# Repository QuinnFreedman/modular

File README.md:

This project is an attempt to make Eurorack modular synthesis affordable and accessible to everyone.

This repository contains open source software and hardware schematics for Eurorack modules which are designed to be assembled easily and cheaply without any technical knowledge. Every module should be able to be assembled for around $20 in about an hour of work, even with limited experience.

To get started, check out some of the links below. Or get in touch! Send me a message at <a href="mailto:freemodular@gmail.com">freemodular@gmail.com</a>. Follow my <a href="https://www.reddit.com/user/FreeModular/submitted/">reddit</a>, <a href="https://freemodular.etsy.com/">Etsy shop</a>, or <a href="https://github.com/QuinnFreedman/modular">GitHub</a>.

**Happy travels on your modular journey!**

<a style="display:none" href="https://freemodular.org">Go to the website to see more</a>

<h2 style="display:none">Links</h2>
<ul class="fm-index-links-container">
  <li>
    <a href="https://freemodular.org/docs/about-eurorack" class="fm-hidden-link fm-index-link">
      About Eurorack
    </a>
  </li>
  <li>
    <a href="https://freemodular.org/docs/assembly" class="fm-hidden-link fm-index-link">
      Assembly Instructions
    </a>
  </li>
  <li>
    <a href="https://freemodular.org/docs/components" class="fm-hidden-link fm-index-link">
      Get Components
    </a>
  </li>
  <li>
    <a href="https://freemodular.org/docs/peripherals" class="fm-hidden-link fm-index-link">
      Accessories
    </a>
  </li>
  <li>
    <a href="https://freemodular.org/docs/appendixn" class="fm-hidden-link fm-index-link">
      Other Resources
    </a>
  </li>
  <li>
    <a href="https://freemodular.org/docs/license" class="fm-hidden-link fm-index-link">
      License
    </a>
  </li>
</ul>

<h2 style="display:none">Modules</h2>
<ul style="display:none">
  <li><a href="https://freemodular.org/modules/Clock">Clock</a></li>
  <li><a href="https://freemodular.org/modules/Envelope">Envelope</a></li>
  <li><a href="https://freemodular.org/modules/RNG">RNG</a></li>
  <li><a href="https://freemodular.org/modules/OffsetAtten">Offset/Atten</a></li>
  <li><a href="https://freemodular.org/modules/Mixer">Mixer</a></li>
  <li><a href="https://freemodular.org/modules/Output">Output</a></li>
  <li><a href="https://freemodular.org/modules/Drift">Drift</a></li>
  <li><a href="https://freemodular.org/modules/Boost">Boost</a></li>
</ul>

{% include_relative docs/modules.md %}

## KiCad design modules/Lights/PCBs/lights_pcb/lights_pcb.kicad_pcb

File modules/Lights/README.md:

<div class="fm-readme-container">
<div class="fm-row">

<div class="fm-readme-text">

<h1>Lights</h1>

<p>Lights allows you to control almost any kind of LED strip or smart LED matrix from your Eurorack case (WS2811, WS2812B, WS2815, or PWM). Lights has 2 LED outputs: one for addressable LED strips that can play various animations and visualizations, and one for solid-color RGB strips, like room lighting.</p>

<p>Lights lets you power those strips from an external power supply, so you don't overload your Eurorack power supply, while keeping the signals <b>totally electrically isolated</b> so there is no risk of ground loops or adding digital noise to your power bus.</p>

<h2>Coming soon</h2>

<p>This module will be available in the next few months. Want to get notified when it releases? <a href="https://mailchi.mp/7a63ae8831d2/get-updated">sign up here</a>. You will get one email when a new module goes live <b>and no other emails.</b></p>

</div>
</div>

</div>

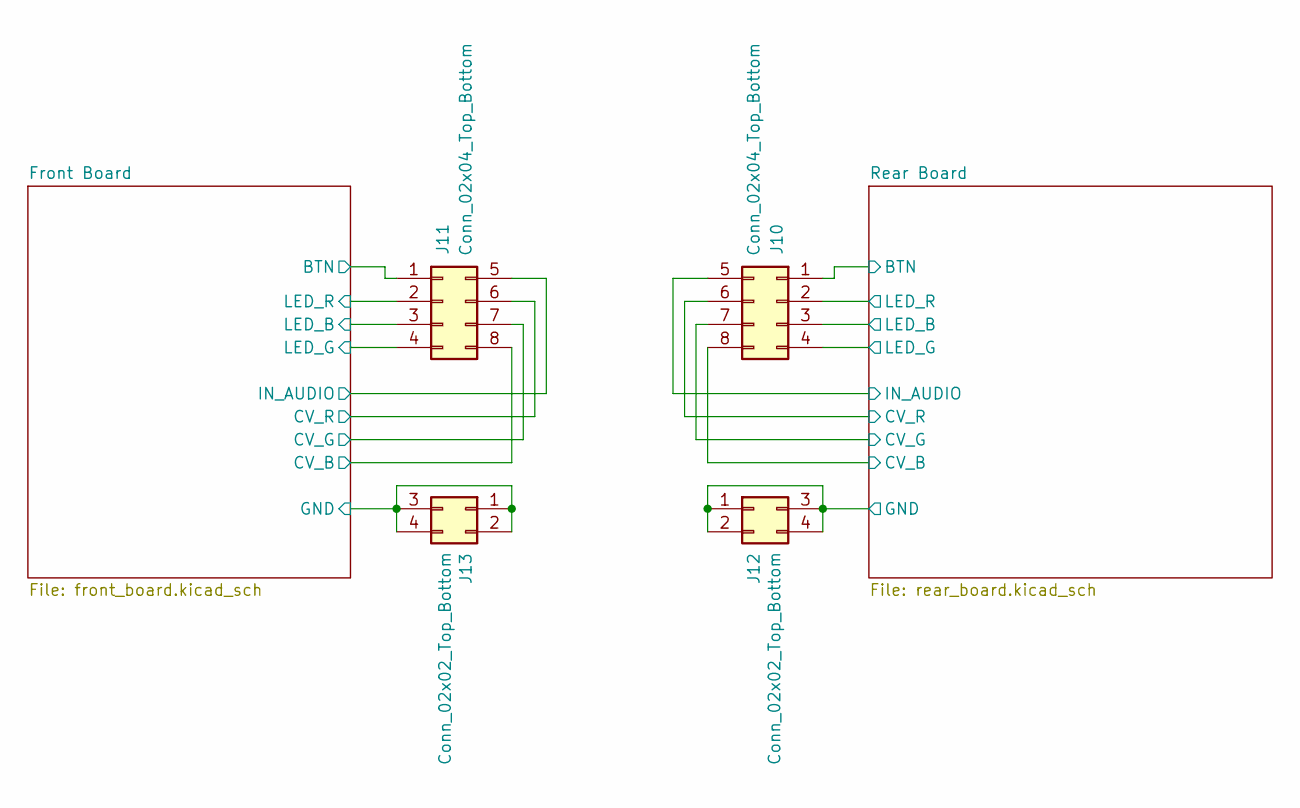
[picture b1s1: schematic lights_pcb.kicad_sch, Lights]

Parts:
J10: Conn_02x04_Top_Bottom; PinSocket_2x04_P2.54mm_Vertical
J11: Conn_02x04_Top_Bottom; PinHeader_2x04_P2.54mm_Horizontal
J12: Conn_02x02_Top_Bottom; PinSocket_2x02_P2.54mm_Vertical
J13: Conn_02x02_Top_Bottom; PinHeader_2x02_P2.54mm_Horizontal

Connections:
/Front Board/BTN: J11.1; also elsewhere on the board
/Front Board/CV_B: J11.8; also elsewhere on the board
/Front Board/CV_G: J11.7; also elsewhere on the board
/Front Board/CV_R: J11.6; also elsewhere on the board
/Front Board/GND: J13.1, J13.2, J13.3, J13.4; also elsewhere on the board
/Front Board/IN_AUDIO: J11.5; also elsewhere on the board
/Front Board/LED_B: J11.3; also elsewhere on the board
/Front Board/LED_G: J11.4; also elsewhere on the board
/Front Board/LED_R: J11.2; also elsewhere on the board
/Rear Board/BTN: J10.1; also elsewhere on the board
/Rear Board/CV_B: J10.8; also elsewhere on the board
/Rear Board/CV_G: J10.7; also elsewhere on the board
/Rear Board/CV_R: J10.6; also elsewhere on the board
/Rear Board/GND: J12.1, J12.2, J12.3, J12.4; also elsewhere on the board
/Rear Board/IN_AUDIO: J10.5; also elsewhere on the board
/Rear Board/LED_B: J10.3; also elsewhere on the board
/Rear Board/LED_G: J10.4; also elsewhere on the board
/Rear Board/LED_R: J10.2; also elsewhere on the board

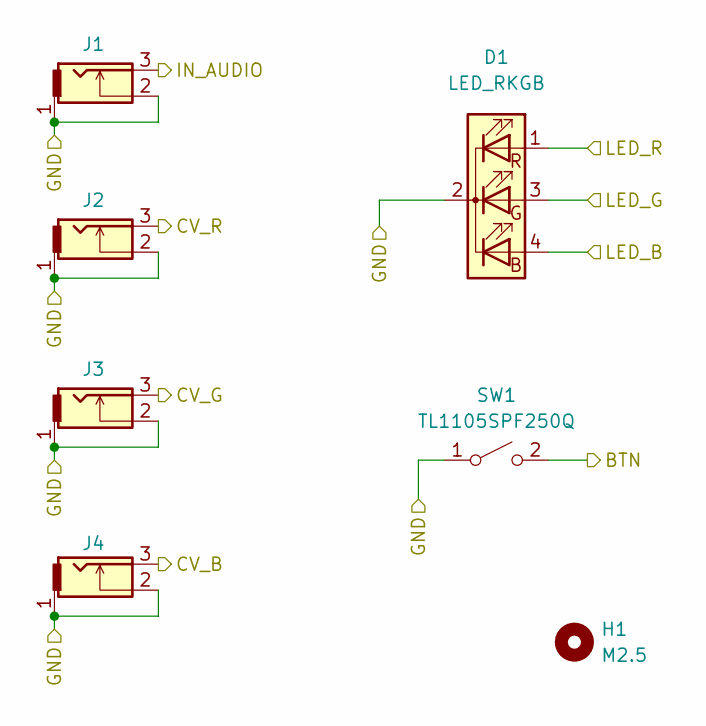
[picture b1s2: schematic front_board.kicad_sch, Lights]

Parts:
D1: LED_RKGB; LED_D5.0mm-4_RGB
H1: M2.5; MountingHole_2.7mm_M2.5
J1, J2, J3, J4: THONKICONN
SW1: TL1105SPF250Q; SW_PUSH_6mm_H13mm

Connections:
/Front Board/BTN: SW1.2 (B); also elsewhere on the board
/Front Board/CV_B: J4.3; also elsewhere on the board
/Front Board/CV_G: J3.3; also elsewhere on the board
/Front Board/CV_R: J2.3; also elsewhere on the board
/Front Board/GND: D1.2 (K), J1.1, J1.2, J2.1, J2.2, J3.1, J3.2, J4.1, J4.2, SW1.1 (A); also elsewhere on the board
/Front Board/IN_AUDIO: J1.3; also elsewhere on the board
/Front Board/LED_B: D1.4 (BA); also elsewhere on the board
/Front Board/LED_G: D1.3 (GA); also elsewhere on the board
/Front Board/LED_R: D1.1 (RA); also elsewhere on the board

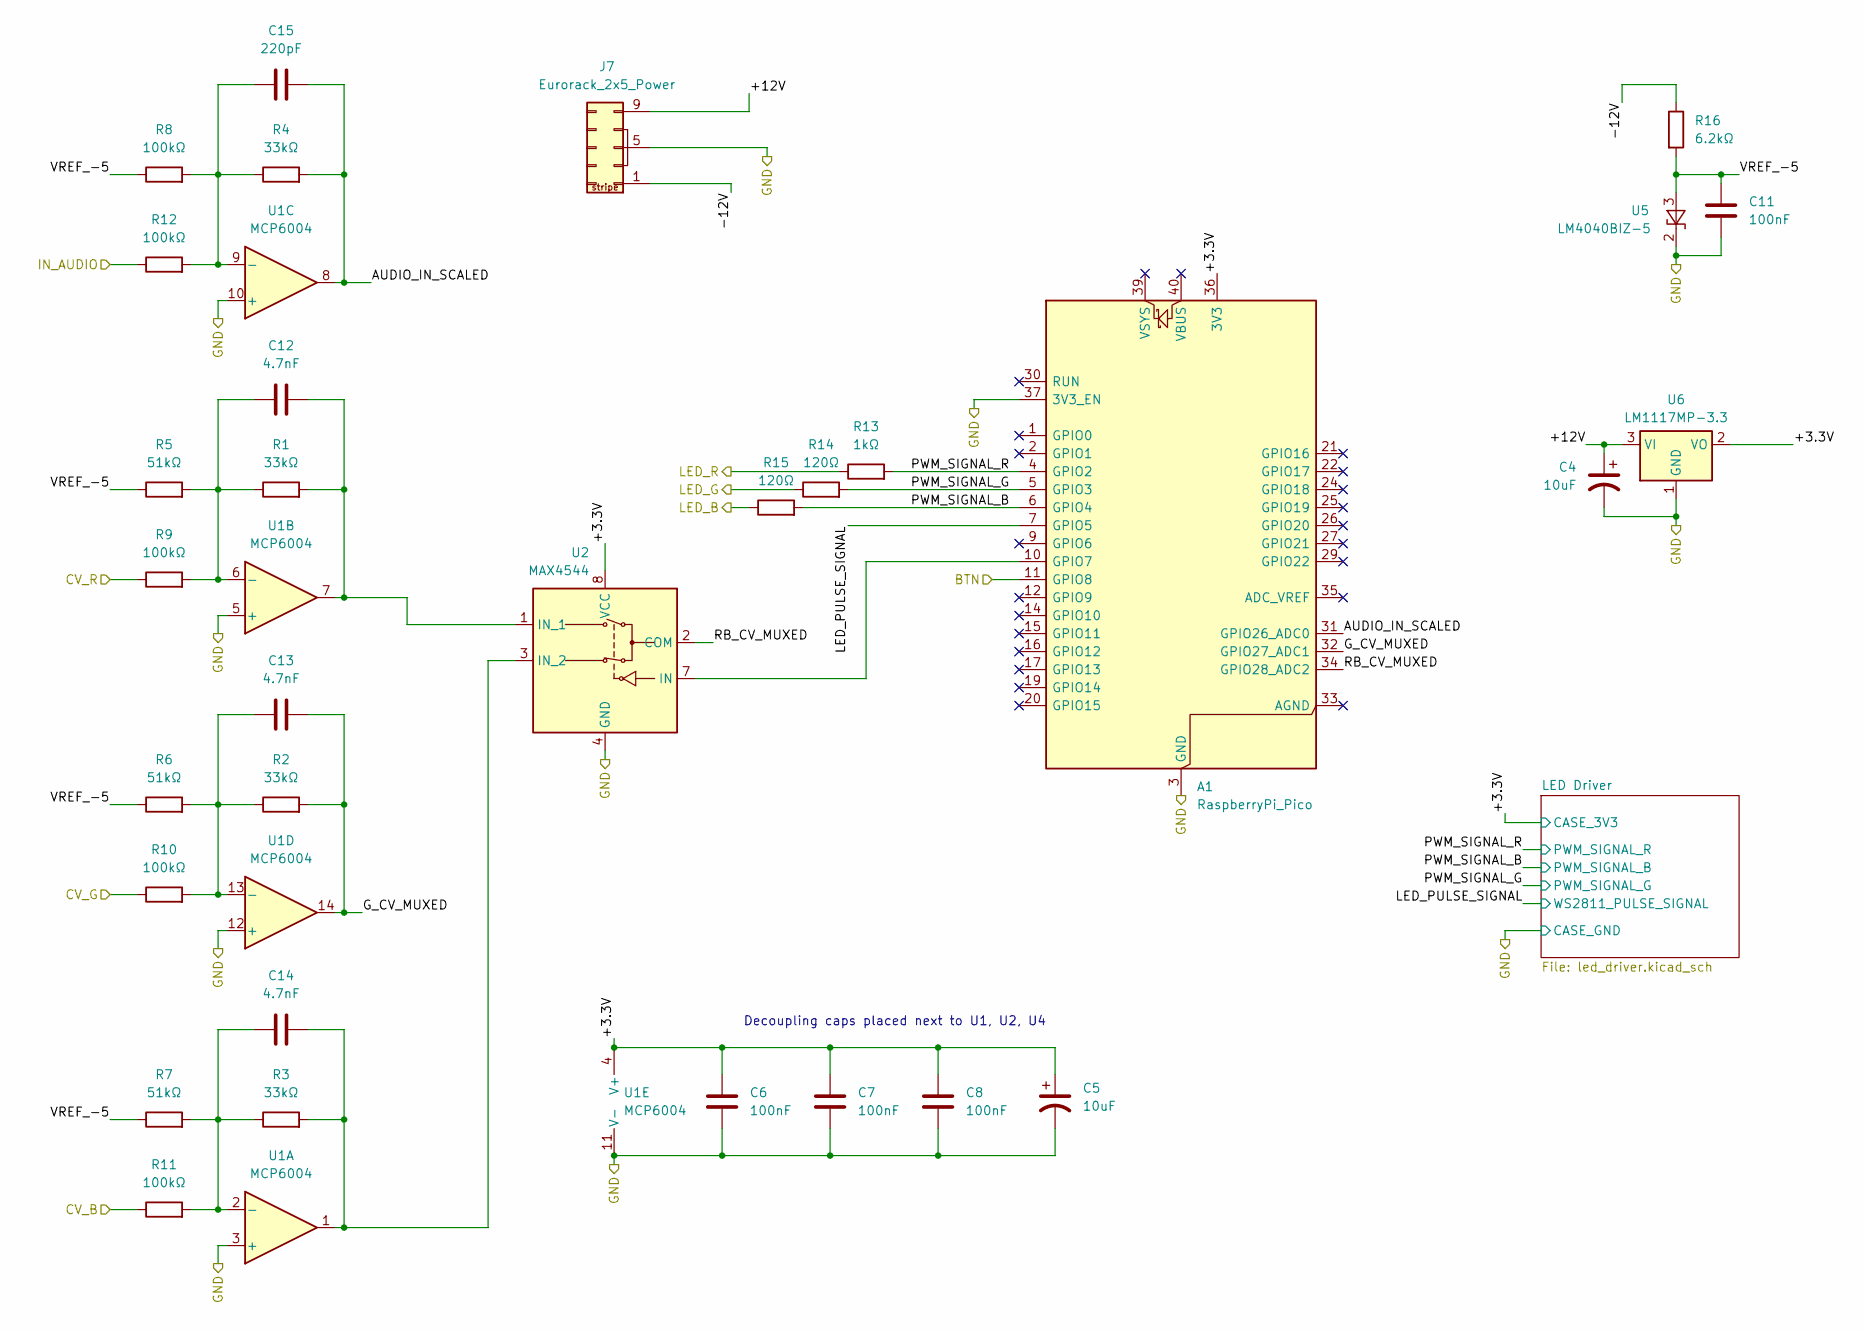
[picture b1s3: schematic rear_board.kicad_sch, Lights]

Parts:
A1: RaspberryPi_Pico; RaspberryPi_Pico_Common_Unspecified
C4, C5: 10uF; CP_Radial_D4.0mm_P1.50mm
C6, C7, C8, C11: 100nF; C_Disc_D5.0mm_W2.5mm_P5.00mm
C12, C13, C14: 4.7nF; C_Disc_D5.0mm_W2.5mm_P5.00mm
C15: 220pF; C_Disc_D5.0mm_W2.5mm_P5.00mm
J7: Eurorack_2x5_Power; IDC-Header_2x05_P2.54mm_Vertical
R1, R2, R3, R4: 33kΩ; R_Axial_DIN0207_L6.3mm_D2.5mm_P7.62mm_Horizontal
R5, R6, R7: 51kΩ; R_Axial_DIN0207_L6.3mm_D2.5mm_P7.62mm_Horizontal
R8, R9, R10, R11, R12: 100kΩ; R_Axial_DIN0207_L6.3mm_D2.5mm_P7.62mm_Horizontal
R13: 1kΩ; R_Axial_DIN0207_L6.3mm_D2.5mm_P7.62mm_Horizontal
R14, R15: 120Ω; R_Axial_DIN0207_L6.3mm_D2.5mm_P7.62mm_Horizontal
R16: 6.2kΩ; R_Axial_DIN0207_L6.3mm_D2.5mm_P7.62mm_Horizontal
U1: MCP6004; DIP-14_W7.62mm
U2: MAX4544; JEITA_SOIC-8_3.9x4.9mm_P1.27mm
U5: LM4040BIZ-5; TO-92_Inline_Wide
U6: LM1117MP-3.3; SOT-223-3_TabPin2

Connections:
/Rear Board/+3.3V: A1.36 (3V3), C5.1, C6.1, C7.1, C8.1, U1.4 (V+), U2.8 (VCC), U6.2 (VO); also elsewhere on the board
/Rear Board/+12V: C4.1, J7.9 (+12v), J7.10 (+12v), U6.3 (VI)
/Rear Board/-12V: J7.1 (-12v), J7.2 (-12v), R16.1
/Rear Board/AUDIO_IN_SCALED: A1.31 (GPIO26_ADC0), C15.2, R4.2, U1.8
/Rear Board/BTN: A1.11 (GPIO8); also elsewhere on the board
/Rear Board/CV_B: R11.1; also elsewhere on the board
/Rear Board/CV_G: R10.1; also elsewhere on the board
/Rear Board/CV_R: R9.1; also elsewhere on the board
/Rear Board/GND: A1.3 (GND), A1.8 (GND), A1.13 (GND), A1.18 (GND), A1.23 (GND), A1.28 (GND), A1.37 (3V3_EN), A1.38 (GND), C4.2, C5.2, C6.2, C7.2, C8.2, C11.2, J7.3 (GND), J7.4 (GND), J7.5 (GND), J7.6 (GND), J7.7 (GND), J7.8 (GND), U1.3 (+), U1.5 (+), U1.10 (+), U1.11 (V-), U1.12 (+), U2.4 (GND), U5.2 (K), U6.1 (GND); also elsewhere on the board
/Rear Board/G_CV_MUXED: A1.32 (GPIO27_ADC1), C13.2, R2.2, U1.14
/Rear Board/IN_AUDIO: R12.1; also elsewhere on the board
/Rear Board/LED_B: R15.1; also elsewhere on the board
/Rear Board/LED_G: R14.1; also elsewhere on the board
/Rear Board/LED_PULSE_SIGNAL: A1.7 (GPIO5); also elsewhere on the board
/Rear Board/LED_R: R13.1; also elsewhere on the board
/Rear Board/PWM_SIGNAL_B: A1.6 (GPIO4), R15.2; also elsewhere on the board
/Rear Board/PWM_SIGNAL_G: A1.5 (GPIO3), R14.2; also elsewhere on the board
/Rear Board/PWM_SIGNAL_R: A1.4 (GPIO2), R13.2; also elsewhere on the board
/Rear Board/RB_CV_MUXED: A1.34 (GPIO28_ADC2), U2.2 (COM)
/Rear Board/VREF_-5: C11.1, R5.1, R6.1, R7.1, R8.1, R16.2, U5.3 (A)
unnamed: A1.10 (GPIO7), U2.7 (IN)
unnamed: C14.1, R3.1, R7.2, R11.2, U1.2 (-)
unnamed: C12.1, R1.1, R5.2, R9.2, U1.6 (-)
unnamed: C15.1, R4.1, R8.2, R12.2, U1.9 (-)
unnamed: C13.1, R2.1, R6.2, R10.2, U1.13 (-)
unnamed: C12.2, R1.2, U1.7, U2.1 (IN_1)
unnamed: C14.2, R3.2, U1.1, U2.3 (IN_2)

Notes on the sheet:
Decoupling caps placed next to U1, U2, U4

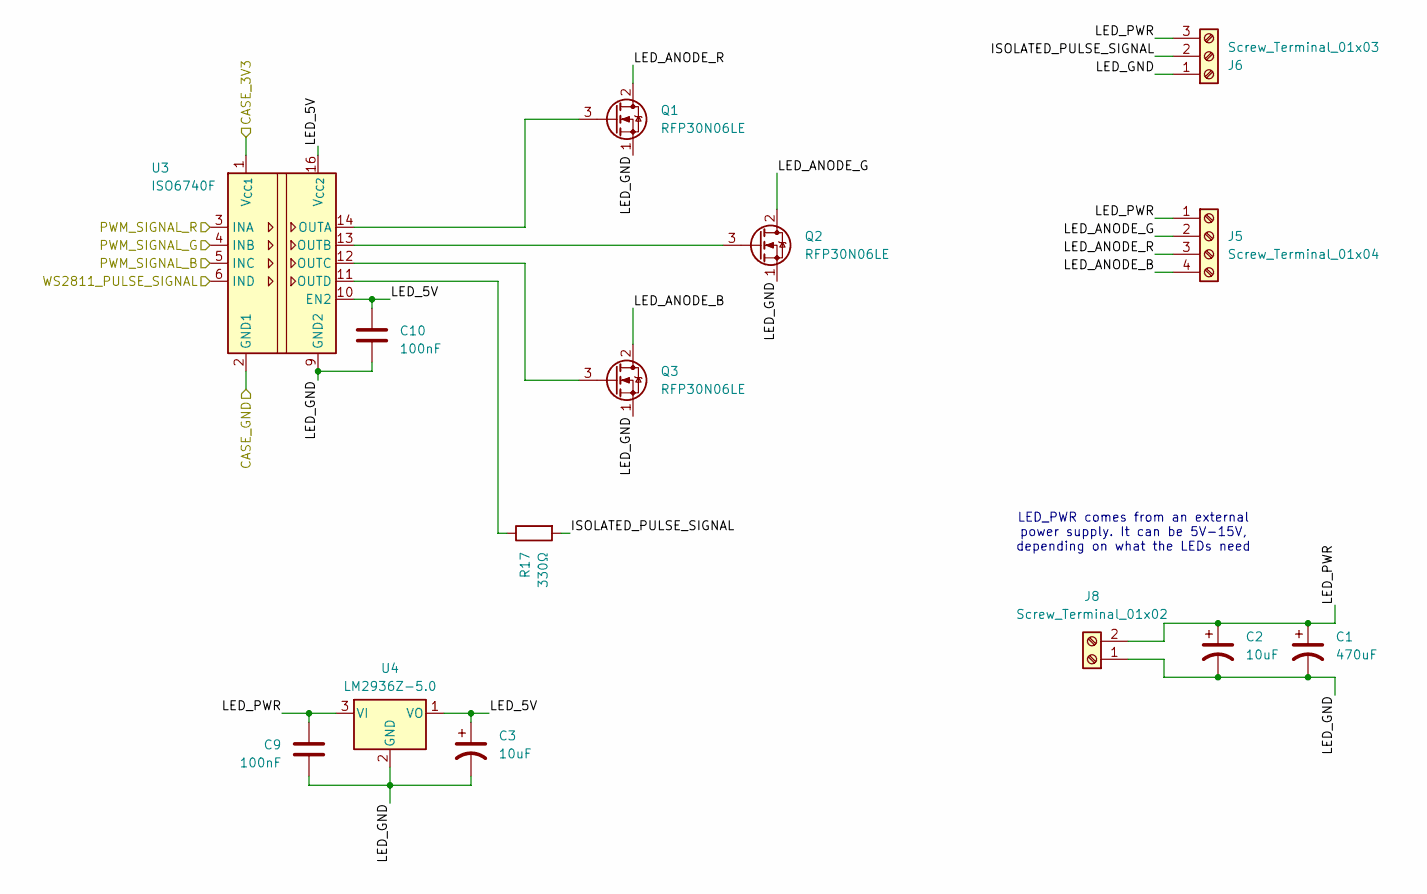
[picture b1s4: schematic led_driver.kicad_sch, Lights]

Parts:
C1: 470uF; CP_Radial_D8.0mm_P3.50mm
C2, C3: 10uF; CP_Radial_D4.0mm_P1.50mm
C9, C10: 100nF; C_Disc_D5.0mm_W2.5mm_P5.00mm
J5: Screw_Terminal_01x04; TerminalBlock_MaiXu_MX126-5.0-04P_1x04_P5.00mm
J6: Screw_Terminal_01x03; TerminalBlock_MaiXu_MX126-5.0-03P_1x03_P5.00mm
J8: Screw_Terminal_01x02; TerminalBlock_MaiXu_MX126-5.0-02P_1x02_P5.00mm
Q1, Q2, Q3: RFP30N06LE; TO-220-3_Vertical
R17: 330Ω; R_Axial_DIN0207_L6.3mm_D2.5mm_P7.62mm_Horizontal
U3: ISO6740F; SOIC-16W_7.5x10.3mm_P1.27mm
U4: LM2936Z-5.0; TO-92_Inline

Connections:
/Rear Board/+3.3V: U3.1 (V_{CC1}); also elsewhere on the board
/Rear Board/GND: U3.2 (GND1), U3.8 (GND1); also elsewhere on the board
/Rear Board/LED Driver/ISOLATED_PULSE_SIGNAL: J6.2, R17.2
/Rear Board/LED Driver/LED_5V: C3.1, C10.1, U3.10 (EN2), U3.16 (V_{CC2}), U4.1 (VO)
/Rear Board/LED Driver/LED_ANODE_B: J5.4, Q3.2 (D)
/Rear Board/LED Driver/LED_ANODE_G: J5.2, Q2.2 (D)
/Rear Board/LED Driver/LED_ANODE_R: J5.3, Q1.2 (D)
/Rear Board/LED Driver/LED_GND: C1.2, C2.2, C3.2, C9.2, C10.2, J6.1, J8.1, Q1.1 (S), Q2.1 (S), Q3.1 (S), U3.9 (GND2), U3.15 (GND2), U4.2 (GND)
/Rear Board/LED Driver/LED_PWR: C1.1, C2.1, C9.1, J5.1, J6.3, J8.2, U4.3 (VI)
/Rear Board/LED_PULSE_SIGNAL: U3.6 (IND); also elsewhere on the board
/Rear Board/PWM_SIGNAL_B: U3.5 (INC); also elsewhere on the board
/Rear Board/PWM_SIGNAL_G: U3.4 (INB); also elsewhere on the board
/Rear Board/PWM_SIGNAL_R: U3.3 (INA); also elsewhere on the board
unnamed: Q1.3 (G), U3.14 (OUTA)
unnamed: Q2.3 (G), U3.13 (OUTB)
unnamed: Q3.3 (G), U3.12 (OUTC)
unnamed: R17.1, U3.11 (OUTD)

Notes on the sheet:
LED_PWR comes from an external power supply. It can be 5V-15V, depending on what the LEDs need

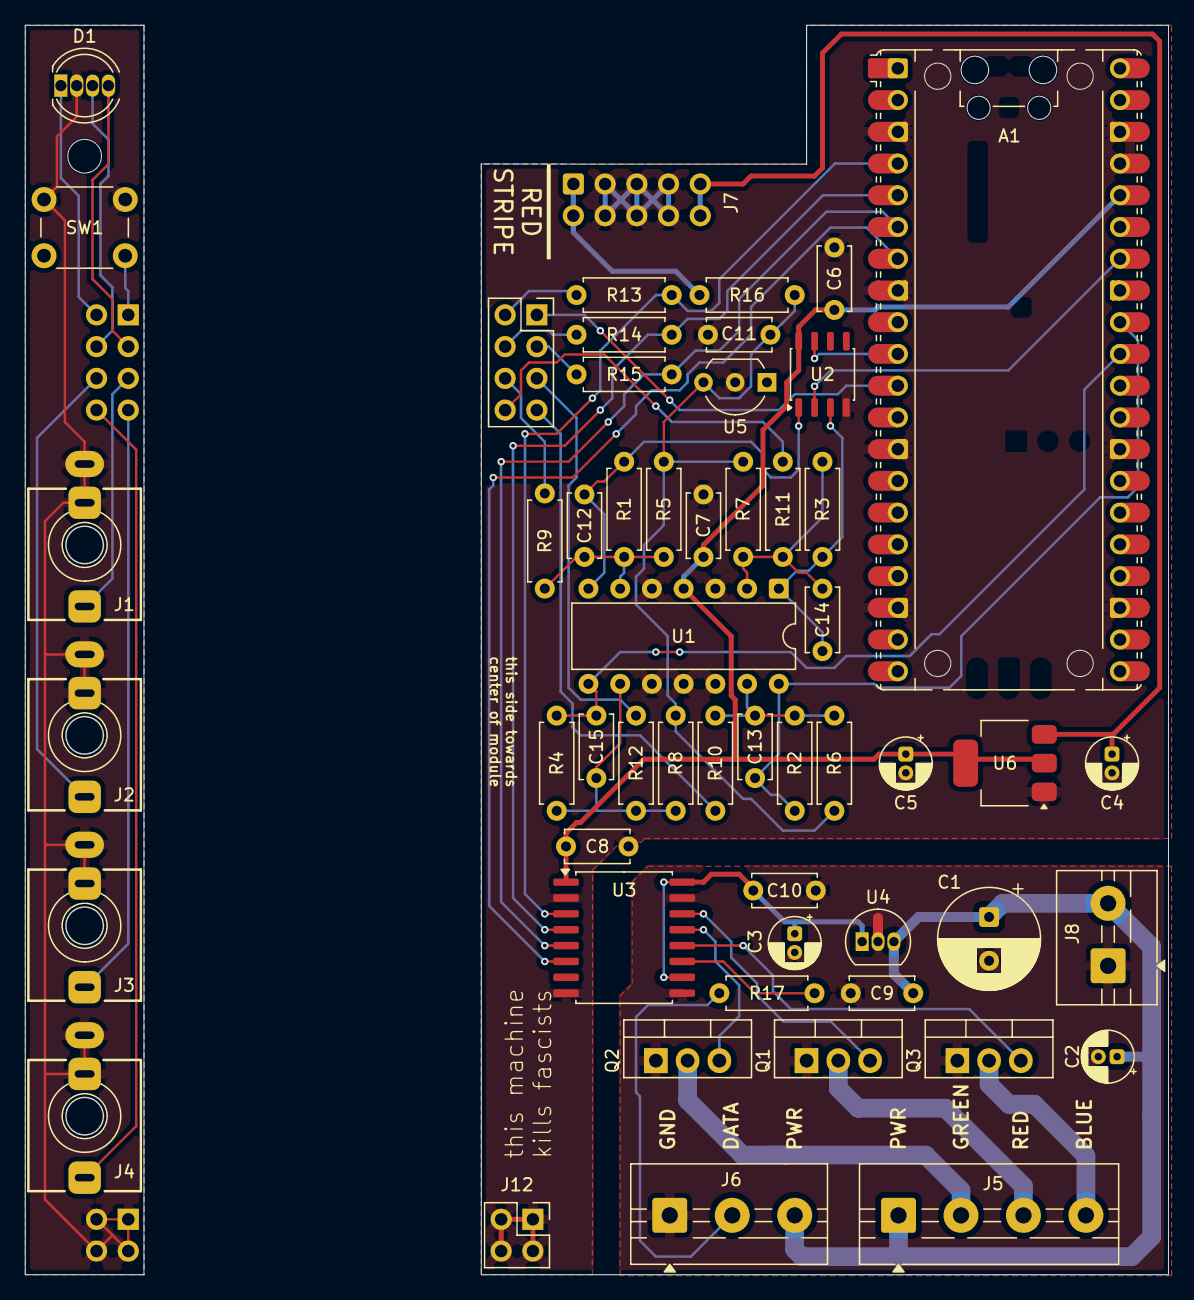
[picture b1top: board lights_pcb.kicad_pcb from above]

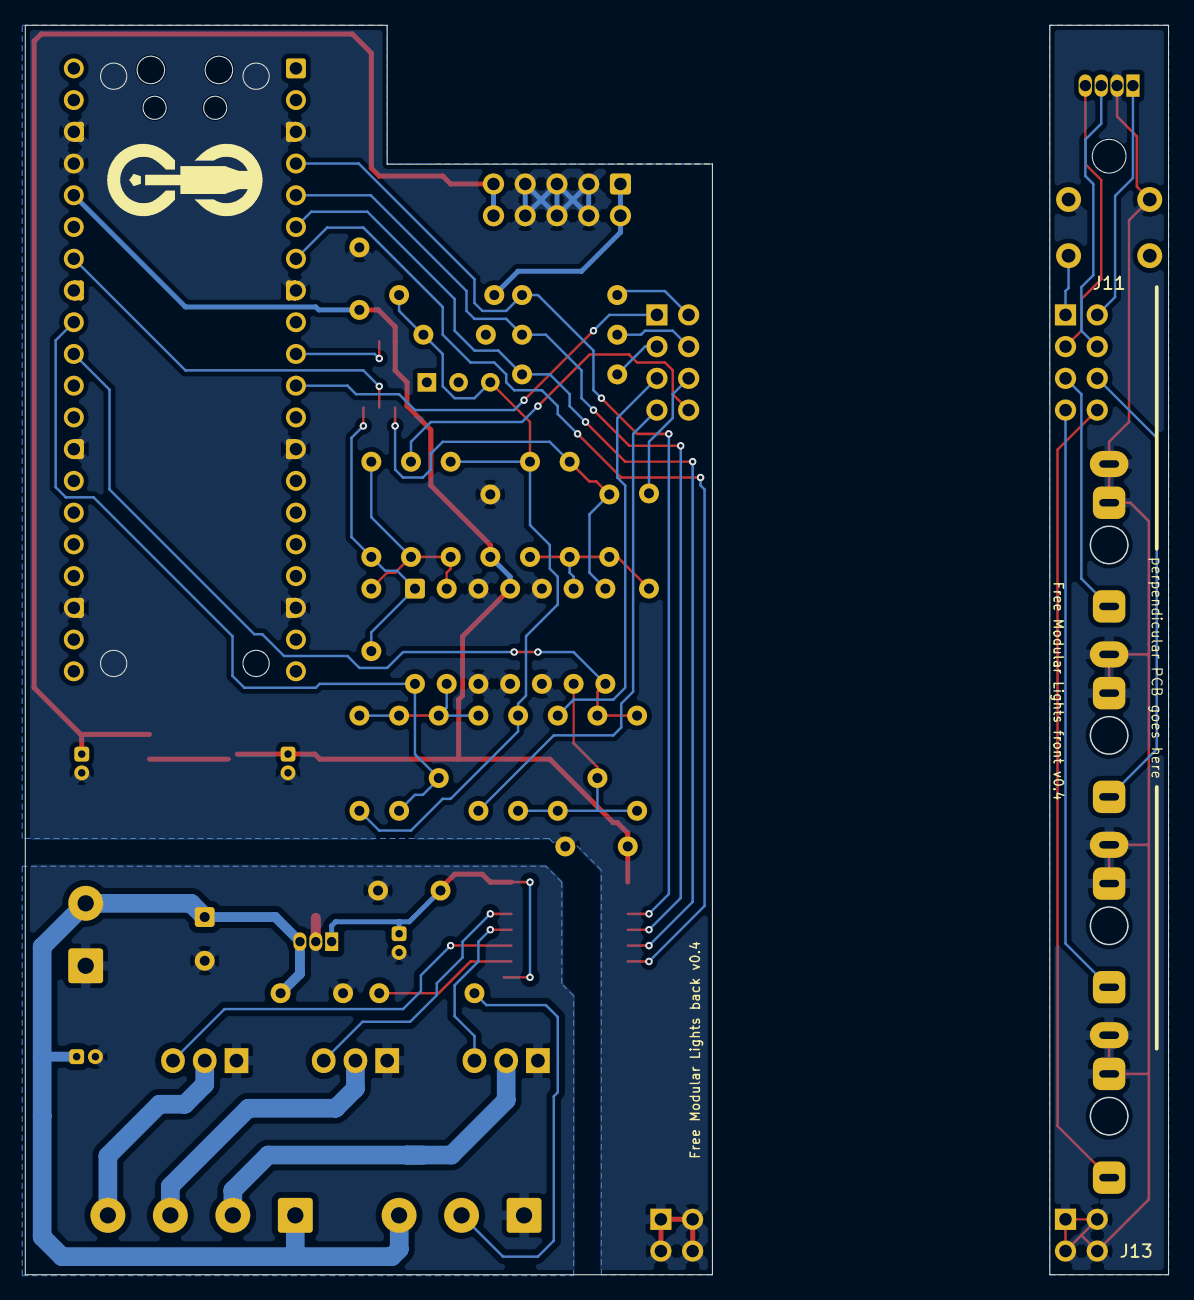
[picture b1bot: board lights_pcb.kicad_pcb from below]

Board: 2 copper layers, 55.0 x 100.0 mm, 59 parts (4 on the bottom side), 47 nets.

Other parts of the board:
B1, B2: Board

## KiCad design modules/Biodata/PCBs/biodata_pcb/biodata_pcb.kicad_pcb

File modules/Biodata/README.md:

<div class="fm-readme-container">
<div class="fm-row">

<div class="fm-readme-text">

<h1>Biodata</h1>

<p>Listen to plants! Generate pitch CV, gates, and raw waveforms from any biological signal. Using TENS cables (with clips or pads), Biodata listens to plants, fungi, people, or even other electronics. Based on the fluctuating electrical resistance between the probes as the subject moves or photosynthesizes, Biodata will generate quantized pitch CV and gates, as well as a raw waveform and smooth CV.</p>

<h2>Resources</h2>

<ul>
  <li><a href="https://quinnfreedman.github.io/fm-artifacts/Biodata/biodata_manual.pdf">Manual</a></li>
  <li><a href="https://quinnfreedman.github.io/modular/modules/Biodata/docs/assembly_instructions">Assembly instructions and BOM</a></li>
  <li>Interactive BOM: <a href="https://quinnfreedman.github.io/fm-artifacts/Biodata/biodata_front_pcb_interactive_bom.html">front panel</a>, <a href="https://quinnfreedman.github.io/fm-artifacts/Biodata/biodata_back_pcb_interactive_bom.html">back panel</a></li>
  <li><a href="https://quinnfreedman.github.io/fm-artifacts/Biodata/biodata_faceplate.svg">Faceplate stencil SVG</a></li>
  <li>GERBER files:
    <ul>
      <li>Faceplate: <a href="https://quinnfreedman.github.io/fm-artifacts/Biodata/biodata_faceplate_jlcpcb.zip">JLCPCB</a>, <a href="https://quinnfreedman.github.io/fm-artifacts/Biodata/biodata_faceplate_pcbway.zip">PCBway</a></li>
      <li>Front panel: <a href="https://quinnfreedman.github.io/fm-artifacts/Biodata/biodata_pcb_front_jlcpcb.zip">JLCPCB</a>, <a href="https://quinnfreedman.github.io/fm-artifacts/Biodata/biodata_pcb_front_pcbway.zip">PCBway</a></li>
      <li>Back panel: <a href="https://quinnfreedman.github.io/fm-artifacts/Biodata/biodata_pcb_back_jlcpcb.zip">JLCPCB</a>, <a href="https://quinnfreedman.github.io/fm-artifacts/Biodata/biodata_pcb_back_pcbway.zip">PCBway</a></li>
    </ul>
  </li>
  <li><a href="https://freemodular.org/modules/Biodata/fm_biodata_tayda_bom.csv">Tayda quick-order CSV</a> (incomplete)</li>
  <li><a href="https://quinnfreedman.github.io/fm-artifacts/Biodata/fm-biodata.hex">Firmware HEX</a></li>
  <li><a href="https://github.com/QuinnFreedman/modular/tree/main/modules/Biodata">Source code</a></li>
  <li><a href="https://quinnfreedman.github.io/fm-artifacts/Biodata/biodata_schematic.pdf">Schematic</a></li>
</ul>

</div>
</div>

<h2>Details</h2>

<b>DIY difficulty:</b> Easy<br>
<b>HP:</b> 6<br>
<b>Power usage:</b>
<table class="fm-current-table">
  <tr>
    <th></th>
    <th>Typical current</th>
    <th>Absolute maximum current</th>
  </tr>
  <tr>
    <td>+5V</td>
    <td>65mA</td>
    <td>75mA</td>
  </tr>
  <tr>
    <td>+12V</td>
    <td>4mA</td>
    <td>24mA</td>
  </tr>
  <tr>
    <td>-12V</td>
    <td>4mA</td>
    <td>5mA</td>
  </tr>
</table>

</div>

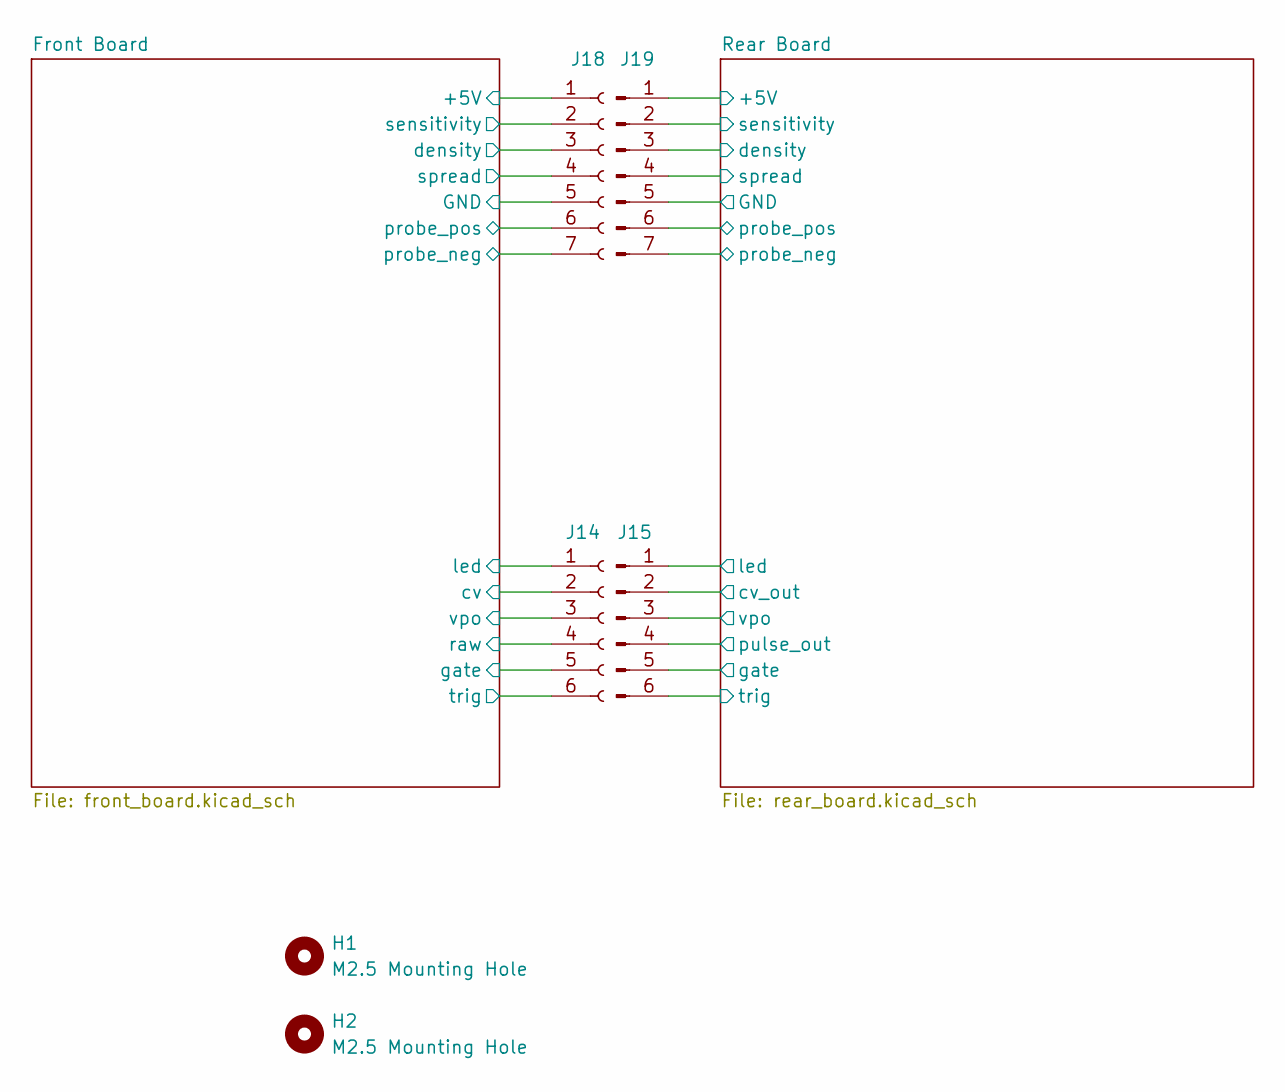
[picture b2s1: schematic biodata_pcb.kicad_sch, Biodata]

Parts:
H1, H2: M2.5 Mounting Hole; MountingHole_2.7mm_M2.5
J14: Conn_01x06_Socket; PinSocket_1x06_P2.54mm_Vertical
J15: Conn_01x06_Pin; PinSocket_1x06_P2.54mm_Vertical
J18: Conn_01x07_Socket; PinSocket_1x07_P2.54mm_Vertical
J19: Conn_01x07_Pin; PinSocket_1x07_P2.54mm_Vertical

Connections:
/Front Board/+5V: J18.1; also elsewhere on the board
/Front Board/GND: J18.5; also elsewhere on the board
/Front Board/cv: J14.2; also elsewhere on the board
/Front Board/density: J18.3; also elsewhere on the board
/Front Board/gate: J14.5; also elsewhere on the board
/Front Board/led: J14.1; also elsewhere on the board
/Front Board/probe_neg: J18.7; also elsewhere on the board
/Front Board/probe_pos: J18.6; also elsewhere on the board
/Front Board/raw: J14.4; also elsewhere on the board
/Front Board/sensitivity: J18.2; also elsewhere on the board
/Front Board/spread: J18.4; also elsewhere on the board
/Front Board/trig: J14.6; also elsewhere on the board
/Front Board/vpo: J14.3; also elsewhere on the board
/Rear Board/+5V: J19.1; also elsewhere on the board
/Rear Board/GND: J19.5; also elsewhere on the board
/Rear Board/cv_out: J15.2; also elsewhere on the board
/Rear Board/density: J19.3; also elsewhere on the board
/Rear Board/gate: J15.5; also elsewhere on the board
/Rear Board/led: J15.1; also elsewhere on the board
/Rear Board/probe_neg: J19.7; also elsewhere on the board
/Rear Board/probe_pos: J19.6; also elsewhere on the board
/Rear Board/pulse_out: J15.4; also elsewhere on the board
/Rear Board/sensitivity: J19.2; also elsewhere on the board
/Rear Board/spread: J19.4; also elsewhere on the board
/Rear Board/trig: J15.6; also elsewhere on the board
/Rear Board/vpo: J15.3; also elsewhere on the board

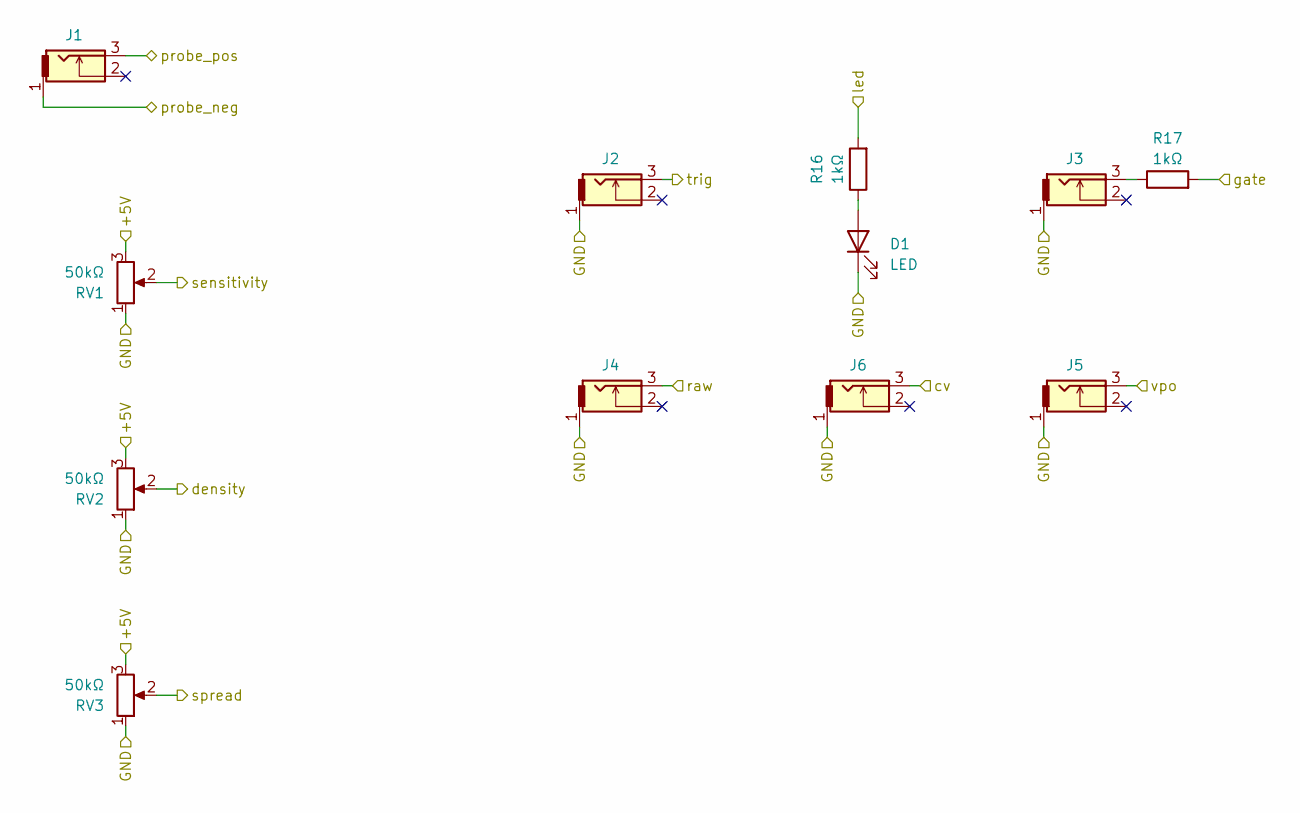
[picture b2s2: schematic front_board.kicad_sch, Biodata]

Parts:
D1: LED; LED_D5.0mm
J1, J2, J3, J4, J5, J6: THONKICONN
R16, R17: 1kΩ; R_Axial_DIN0207_L6.3mm_D2.5mm_P10.16mm_Horizontal
RV1: 50kΩ; Potentiometer_Alpha_RD901F-40-00D_Single_Vertical
RV2, RV3: 50kΩ; Potentiometer_Alpha_Single_Vertical_trim

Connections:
/Front Board/+5V: RV1.3, RV2.3, RV3.3; also elsewhere on the board
/Front Board/GND: D1.1 (K), J2.1, J3.1, J4.1, J5.1, J6.1, RV1.1, RV2.1, RV3.1; also elsewhere on the board
/Front Board/cv: J6.3; also elsewhere on the board
/Front Board/density: RV2.2; also elsewhere on the board
/Front Board/gate: R17.2; also elsewhere on the board
/Front Board/led: R16.2; also elsewhere on the board
/Front Board/probe_neg: J1.1; also elsewhere on the board
/Front Board/probe_pos: J1.3; also elsewhere on the board
/Front Board/raw: J4.3; also elsewhere on the board
/Front Board/sensitivity: RV1.2; also elsewhere on the board
/Front Board/spread: RV3.2; also elsewhere on the board
/Front Board/trig: J2.3; also elsewhere on the board
/Front Board/vpo: J5.3; also elsewhere on the board
unnamed: D1.2 (A), R16.1
unnamed: J3.3, R17.1

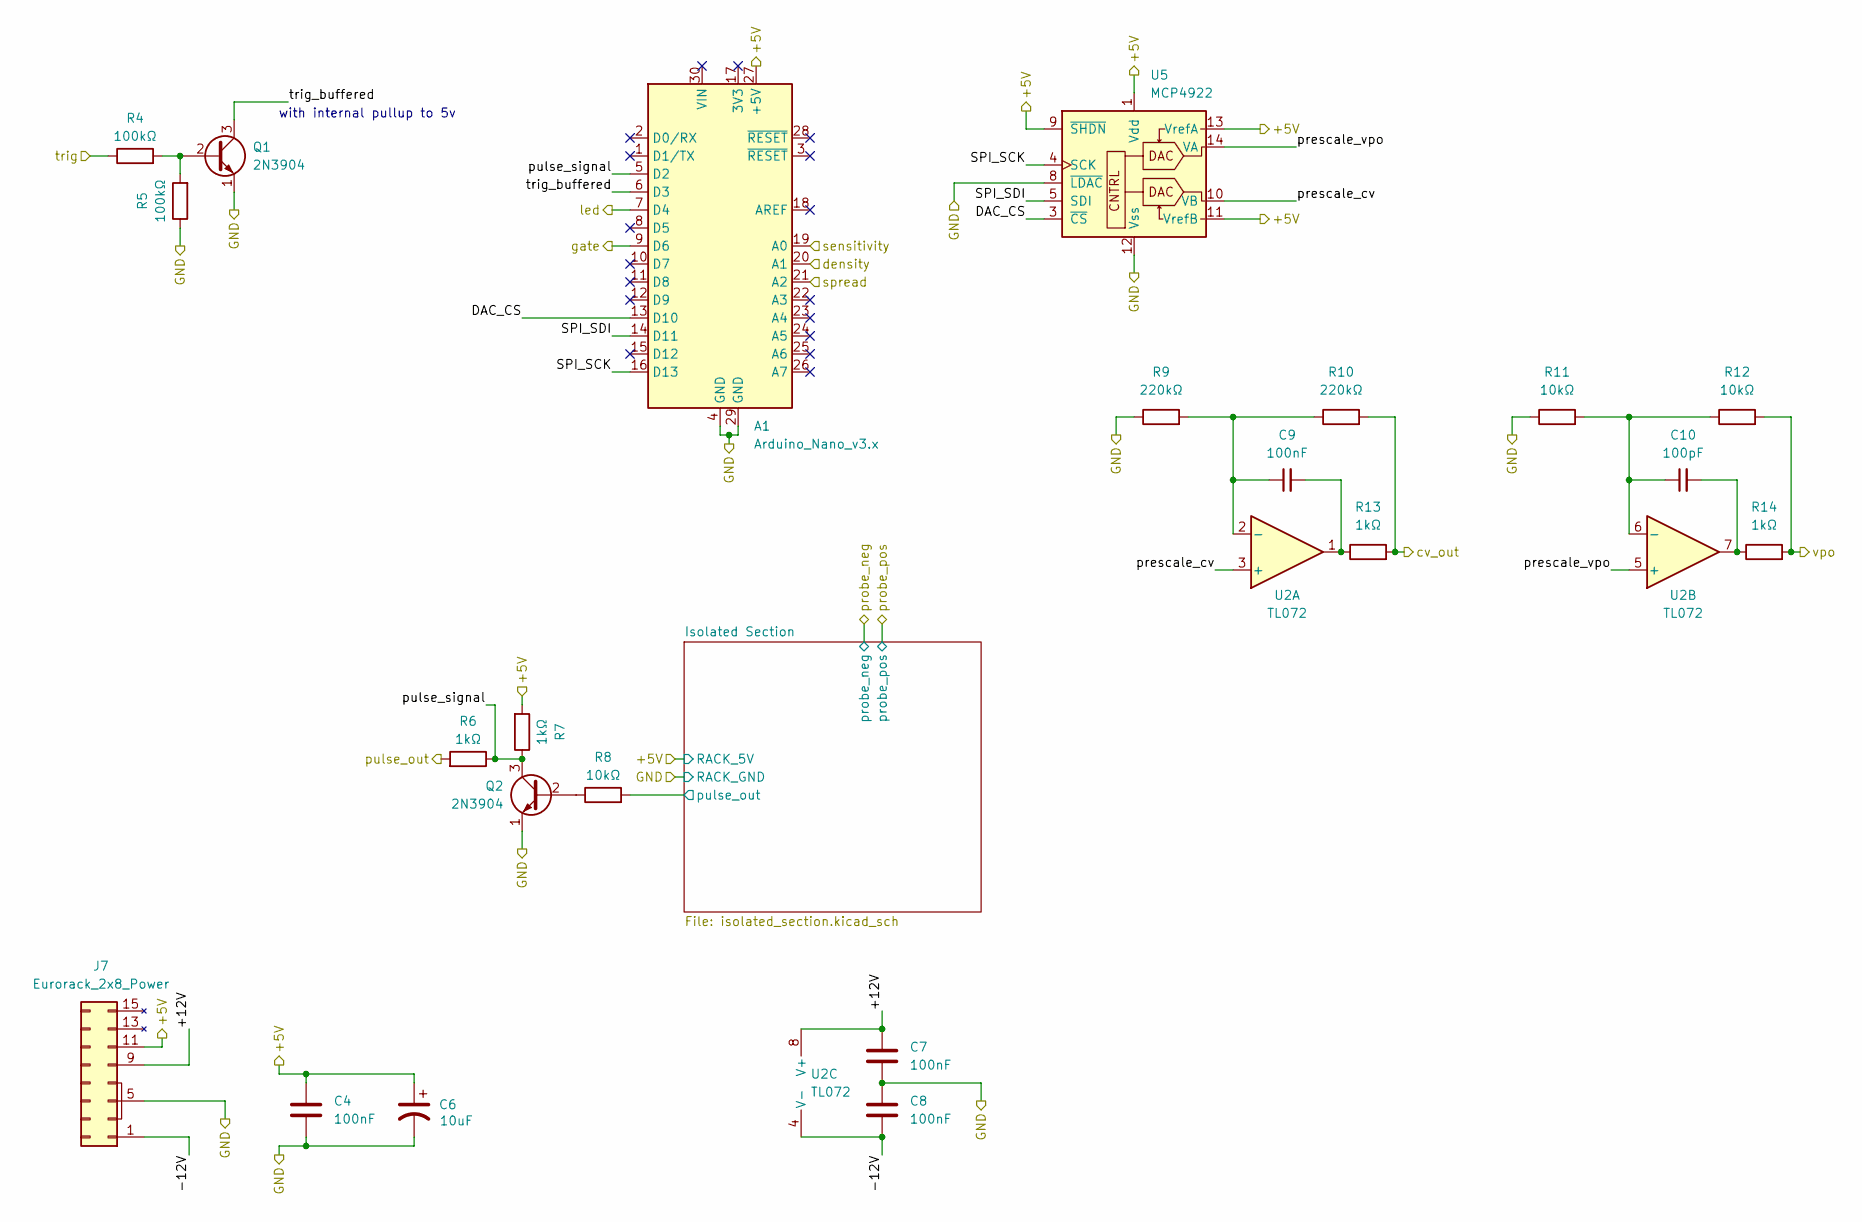
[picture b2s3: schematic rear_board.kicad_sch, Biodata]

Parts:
A1: Arduino_Nano_v3.x; Arduino_Nano
C4, C7, C8, C9: 100nF; C_Disc_D4.7mm_W2.5mm_P5.00mm
C6: 10uF; CP_Radial_D4.0mm_P1.50mm
C10: 100pF; C_Disc_D4.7mm_W2.5mm_P5.00mm
J7: Eurorack_2x8_Power; IDC-Header_2x08_P2.54mm_Vertical
Q1, Q2: 2N3904; TO-92L_Inline_Wide
R4, R5: 100kΩ; R_Axial_DIN0207_L6.3mm_D2.5mm_P10.16mm_Horizontal
R6, R7, R13, R14: 1kΩ; R_Axial_DIN0207_L6.3mm_D2.5mm_P10.16mm_Horizontal
R8, R11, R12: 10kΩ; R_Axial_DIN0207_L6.3mm_D2.5mm_P10.16mm_Horizontal
R9, R10: 220kΩ; R_Axial_DIN0207_L6.3mm_D2.5mm_P10.16mm_Horizontal
U2: TL072; DIP-8_W7.62mm
U5: MCP4922; DIP-14_W7.62mm

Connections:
/Rear Board/+5V: A1.27 (+5V), C4.2, C6.1, J7.11 (+5v), J7.12 (+5v), R7.2, U5.1 (Vdd), U5.9 (~SHDN), U5.11 (VrefB), U5.13 (VrefA); also elsewhere on the board
/Rear Board/+12V: C7.2, J7.9 (+12v), J7.10 (+12v), U2.8 (V+)
/Rear Board/-12V: C8.1, J7.1 (-12v), J7.2 (-12v), U2.4 (V-)
/Rear Board/DAC_CS: A1.13 (D10), U5.3 (~CS)
/Rear Board/GND: A1.4 (GND), A1.29 (GND), C4.1, C6.2, C7.1, C8.2, J7.3 (GND), J7.4 (GND), J7.5 (GND), J7.6 (GND), J7.7 (GND), J7.8 (GND), Q1.1 (E), Q2.1 (E), R5.1, R9.1, R11.1, U5.8 (~LDAC), U5.12 (Vss); also elsewhere on the board
/Rear Board/Isolated Section/pulse_out: R8.2; also elsewhere on the board
/Rear Board/SPI_SCK: A1.16 (D13), U5.4 (SCK)
/Rear Board/SPI_SDI: A1.14 (D11), U5.5 (SDI)
/Rear Board/cv_out: R10.2, R13.2; also elsewhere on the board
/Rear Board/density: A1.20 (A1); also elsewhere on the board
/Rear Board/gate: A1.9 (D6); also elsewhere on the board
/Rear Board/led: A1.7 (D4); also elsewhere on the board
/Rear Board/prescale_cv: U2.3 (+), U5.10 (VB)
/Rear Board/prescale_vpo: U2.5 (+), U5.14 (VA)
/Rear Board/pulse_out: R6.2; also elsewhere on the board
/Rear Board/pulse_signal: A1.5 (D2), Q2.3 (C), R6.1, R7.1
/Rear Board/sensitivity: A1.19 (A0); also elsewhere on the board
/Rear Board/spread: A1.21 (A2); also elsewhere on the board
/Rear Board/trig: R4.1; also elsewhere on the board
/Rear Board/trig_buffered: A1.6 (D3), Q1.3 (C)
/Rear Board/vpo: R12.2, R14.2; also elsewhere on the board
unnamed: C9.2, R13.1, U2.1
unnamed: C10.2, R14.1, U2.7
unnamed: Q1.2 (B), R4.2, R5.2
unnamed: Q2.2 (B), R8.1
unnamed: C9.1, R9.2, R10.1, U2.2 (-)
unnamed: C10.1, R11.2, R12.1, U2.6 (-)

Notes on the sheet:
with internal pullup to 5v
